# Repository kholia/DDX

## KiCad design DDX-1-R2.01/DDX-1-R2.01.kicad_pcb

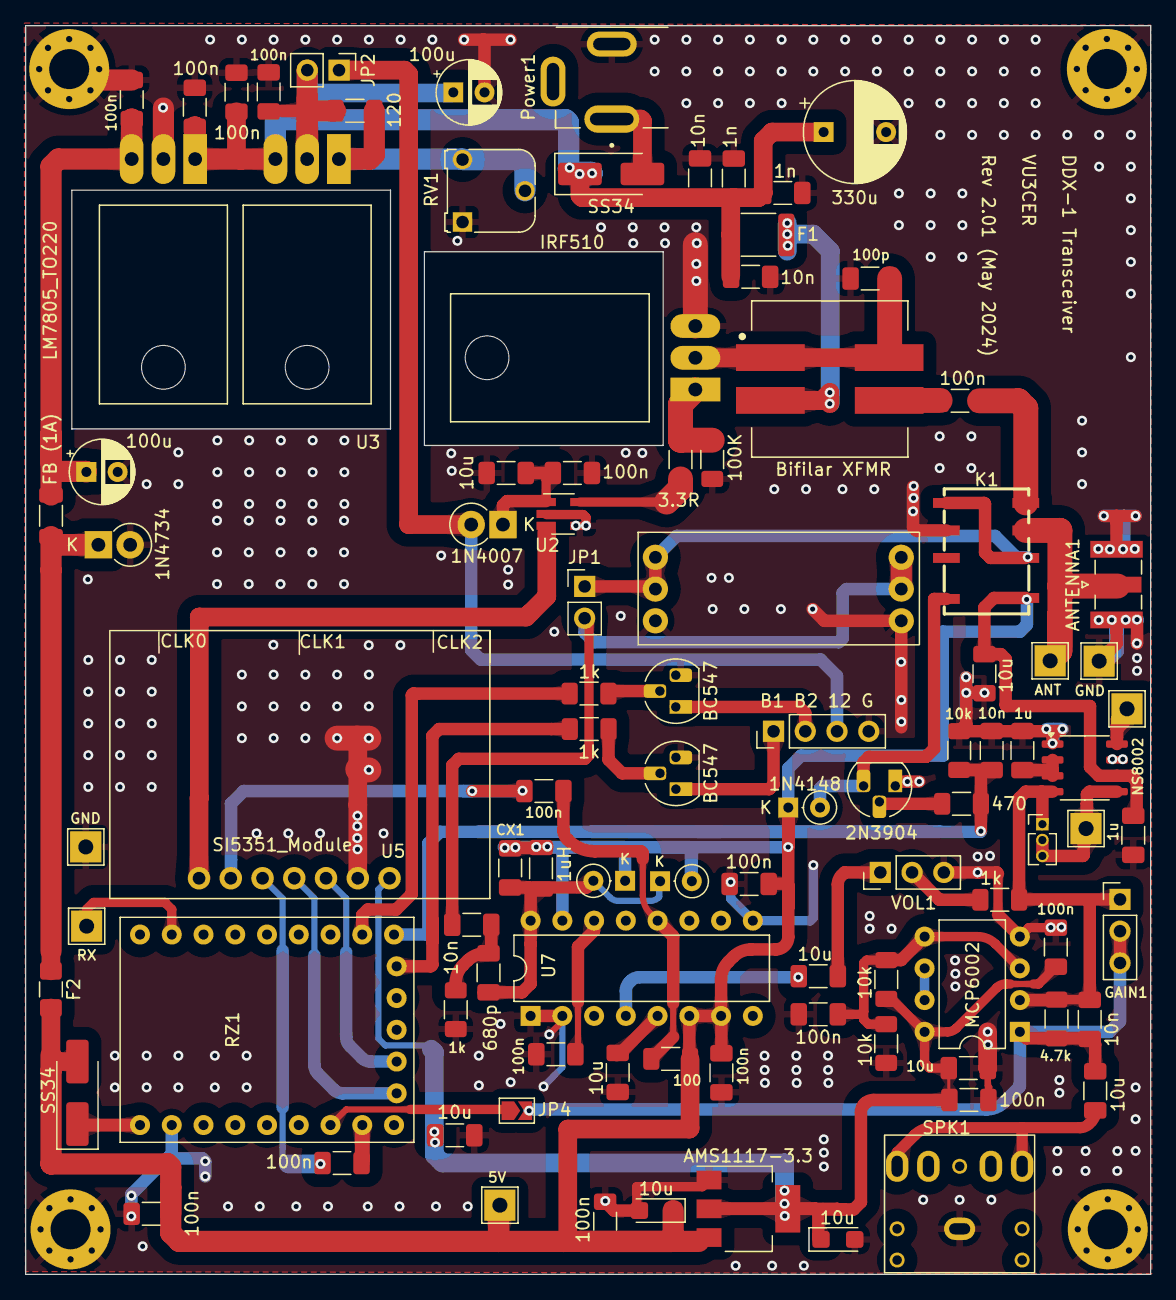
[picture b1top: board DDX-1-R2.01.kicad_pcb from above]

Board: 2 copper layers, 90.0 x 99.9 mm, 102 parts (0 on the bottom side), 54 nets.

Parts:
ANTENNA1: SMA; SMA_Samtec_SMA-J-P-X-ST-EM1_EdgeMount
BPF2: Pluggable SMD BPF; Pluggable-BPF
C1, C7, C9, C16, C21, C25, C26, C27, C28, C29, C30, C32, C37, C39, C41, C47: 100n; C_1206_3216Metric_Pad1.33x1.80mm_HandSolder
C2, C15: 1u; C_1206_3216Metric_Pad1.33x1.80mm_HandSolder
C3: 100p; C_1206_3216Metric_Pad1.33x1.80mm_HandSolder
C4, C6, C11, C35, C40: 10n; C_1206_3216Metric_Pad1.33x1.80mm_HandSolder
C5: 330u; CP_Radial_D8.0mm_P5.00mm
C10, C17: 1n; C_1206_3216Metric_Pad1.33x1.80mm_HandSolder
C12, C13, C23, C36, C38, C42, C43: 10u; C_1206_3216Metric_Pad1.33x1.80mm_HandSolder
C14, C44: 100u; CP_Radial_D5.0mm_P2.50mm
C31: 680p; C_1206_3216Metric_Pad1.33x1.80mm_HandSolder
C45, C46: 10u; CP_EIA-3216-10_Kemet-I
CX1: DNP; C_1206_3216Metric_Pad1.33x1.80mm_HandSolder
D1, D2: SS34; D_SMA_Handsoldering
D3, D8, D9: 1N4148; D_DO-35_SOD27_P2.54mm_Vertical_KathodeUp
D4: 1N4007; D_DO-41_SOD81_P2.54mm_Vertical_KathodeUp
D5: 1N4734; D_DO-41_SOD81_P2.54mm_Vertical_KathodeUp
F1: 2A; Fuse_1812_4532Metric_Pad1.30x3.40mm_HandSolder
F2: 0.5A; Fuse_1206_3216Metric_Pad1.42x1.75mm_HandSolder
GAIN1: 100k; PinHeader_1x03_P2.54mm_Vertical
GAIN2: 250k; PinHeader_1x03_P1.27mm_Vertical
H1, H2, H3, H4: MountingHole_Pad; MountingHole_3.2mm_M3_Pad_Via
J2: E-LPF; PinHeader_1x04_P2.54mm_Vertical
JP1, JP2: Jumper_2_Open; PinHeader_1x02_P2.54mm_Vertical
JP4: Jumper_2_Open; SolderJumper-2_P1.3mm_Open_TrianglePad1.0x1.5mm
K1: HFD4/5-S; RELAY-SMD_HFD4-5-SR
L4: FB (1A); L_1206_3216Metric_Pad1.22x1.90mm_HandSolder
L5: 1uH; L_1206_3216Metric_Pad1.22x1.90mm_HandSolder
Power1: DC-005 (Barrel Jack); XKB_DC-005-5A-2.0_Modded
Q1: 2N3904; TO-92_HandSolder
Q2: IRF510; TO-220-3_Horizontal_TabDown
Q3, Q4: BC547; TO-92_HandSolder
R1: 100K; R_1206_3216Metric_Pad1.30x1.75mm_HandSolder
R2, R10, R11: 10k; R_1206_3216Metric_Pad1.30x1.75mm_HandSolder
R3, R5, R7: 1k; R_1206_3216Metric_Pad1.30x1.75mm_HandSolder
R4: 470; R_1206_3216Metric_Pad1.30x1.75mm_HandSolder
R6: 100; R_1206_3216Metric_Pad1.30x1.75mm_HandSolder
R12: 3.3R; R_1206_3216Metric_Pad1.30x1.75mm_HandSolder
R14: 120; R_1206_3216Metric_Pad1.30x1.75mm_HandSolder
RV1: 5k; Potentiometer_Runtron_RM-065_Vertical
RZ1: RP2040-Zero
Rf1: 4.7k; R_1206_3216Metric_Pad1.30x1.75mm_HandSolder
Rin1: 1k; R_1206_3216Metric_Pad1.30x1.75mm_HandSolder
SPK1: SPEAKER; PJ-307_Modded
T1: Bifilar XFMR; IND_SRF1260A-4R7Y-Longer-Pads
TP1, TP2, TP3, TP4, TP5, TP6, TP7: TestPoint; TestPoint_THTPad_2.5x2.5mm_Drill1.2mm
U1: LM7805_TO220; TO-220-3_Horizontal_TabDown
U2: UCC27517ADBVR; SOT-23-5_HandSoldering
U3: LM1086-ADJ-220; TO-220-3_Horizontal_TabDown
U4: AMS1117-3.3; SOT-223-3_TabPin2
U5: SI5351_Module; SI5351 Module
U6: NS8002; SO-8_3.9x4.9mm_P1.27mm
U7: CD2003GB_GP; DIP-16_W7.62mm
U8: MCP6002; DIP-8_W7.62mm
VOL1: 10k; PinHeader_1x03_P2.54mm_Vertical

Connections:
10m: J2.1, Q3.1 (C)
11v: D4.2 (A), J2.3, JP2.1 (A)
12V: C1.1, C5.1, C6.1, C10.1, C11.1, C17.1, C32.1, D1.1 (K), F1.2, U1.1 (VI), U3.3 (VI)
20m: J2.2, Q4.1 (C)
+3.3V: C12.2, C25.1, C41.1, C42.1, C46.1, R10.1, U4.2 (VO), U5.1 (VIN), U8.8 (V+)
+5V: C13.1, C15.2, C21.1, C28.1, C37.1, C45.1, C47.1, CX1.2, D2.2 (A), D3.1 (K), D8.1 (K), D9.2 (A), F2.2, K1.1, L5.2, R6.2, TP5.1, U4.3 (VI), U6.6 (VDD), U7.6 (VCC), U7.7 (AM_IF), U7.15 (FM_TUNER)
+VDC: D1.2 (A), Power1.1
/DRAIN: C3.1, Q2.2 (D), T1.1, T1.4
ANTENNA: ANTENNA1.1 (In), K1.3, TP3.1
CAL: C27.2, RZ1.16 (GP15)
G1: R5.1, RZ1.8 (GP7)
G2: R3.1, RZ1.10 (GP9)
GND: ANTENNA1.2 (Ext), BPF2.3 (GND), BPF2.6 (GND), C1.2, C2.1, C3.2, C4.2, C5.2, C6.2, C9.2, C10.2, C11.2, C12.1, C13.2, C14.2, C15.1, C16.2, C17.2, C21.2, C23.2, C25.2, C28.2, C29.1, C30.2, C32.2, C36.2, C37.2, C39.2, C41.2, C42.2, C44.2, C45.2, C46.2, C47.2, D5.2 (A), H1.1, H2.1, H3.1, H4.1, J2.4, K1.6, Power1.2, Q1.1 (E), Q2.3 (S), Q3.3 (E), Q4.3 (E), R1.2, R2.2, R7.2, R11.2, RV1.1, RZ1.23 (GND), SPK1.S, TP2.1, TP4.1, U1.2 (GND), U2.2 (GND), U2.4 (IN-), U4.1 (GND), U5.2 (GND), U6.1 (SD), U6.7 (GND), U7.1 (FM_RF_IN), U7.2 (GND_IN), U7.9 (GND_OUT), U8.4 (V-), VOL1.3
unnamed: C7.2, T1.3
unnamed: C31.1, C35.1, R7.1
unnamed: C38.2, VOL1.1
unnamed: C43.2, SPK1.R, SPK1.T
unnamed: D2.1 (K), RZ1.22 (5V)
unnamed: D3.2 (A), K1.8, Q1.3 (C)
unnamed: C16.1, C23.1, D4.1 (K), U2.1 (VDD)
unnamed: D5.1 (K), F2.1, L4.1
unnamed: C31.2, CX1.1, D8.2 (A), D9.1 (K), L5.1, U7.16 (AM_RF_IN)
unnamed: F1.1, T1.2
unnamed: C14.1, C30.1, JP2.2 (B), R14.1, U3.2 (VO)
unnamed: JP4.1 (A), RZ1.17 (GP26)
unnamed: Q1.2 (B), R4.2
unnamed: Q2.1 (G), R1.1, R12.2
unnamed: Q3.2 (B), R3.2
unnamed: Q4.2 (B), R5.2
unnamed: RZ1.2 (GP1), TP1.1
unnamed: Rin1.2, VOL1.2
unnamed: C9.1, C44.1, L4.2, U1.3 (VO)
unnamed: R12.1, U2.5 (OUT)
unnamed: R14.2, RV1.2, RV1.3, U3.1 (ADJ)
unnamed: C27.1, U5.5 (S2)
unnamed: C2.2, U6.2 (Bypass), U6.3 (+IN)
unnamed: GAIN2.2, GAIN2.3, TP7.1, U6.5 (VO1)
unnamed: TP6.1, U6.8 (VO2)
unnamed: C36.1, U7.5 (AGC)
unnamed: C26.1, R6.1, U7.12 (AM_OSC)
unnamed: C29.2, U7.14 (FM/AM_SW)
unnamed: C39.1, R10.2, R11.1, U8.3 (+), U8.5 (+)
unnamed: U8.6 (-), U8.7
PTT: C4.1, R2.1, R4.1, RZ1.9 (GP8)
RF_OUT1: C7.1, K1.4
RIGHT: C40.2, GAIN1.1, GAIN2.1, Rf1.2, Rin1.1, U6.4 (-IN), U8.2 (-)
RX: BPF2.1 (ANT), BPF2.2 (ANT), JP1.1 (A), K1.2, K1.5
RX_AFTER_HPF: BPF2.4 (RF), BPF2.5 (RF), C35.2, JP1.2 (B)
RX_AUDIO: C38.1, U7.4 (AM_MIX)
RX_OSC: C26.2, U5.6 (S1)
SCL: RZ1.14 (GP13), U5.4 (SCL)
SDA: RZ1.13 (GP12), U5.3 (SDA)
TO_ADC: C40.1, C43.1, GAIN1.2, GAIN1.3, JP4.2 (B), Rf1.1, U8.1
TX_RF: U2.3 (IN+), U5.7 (SO)
